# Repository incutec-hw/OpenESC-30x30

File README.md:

# OpenESC-30x30

Open-source 4-in-1 BLDC ESC with a 30.5 × 30.5 mm mounting pattern, built around four independent AT32F421 motor controllers running AM32. Six-layer, DShot over the standard 8-pin connector. Designed in KiCad for JLCPCB assembly.

Part of the incutec OpenDrone line (`incutec-hw/OpenESC-30x30`).

> A smaller **[OpenESC_20X20](https://github.com/incutec-hw/OpenESC_20X20)** (20×20 mm) shares this design and mirrors this repo. The two differ only in board/mounting size and a few power-stage parts.

## Architecture

Four fully independent ESC channels share a common power input and telemetry connector. Each channel has its own MCU and gate driver; the high-current stage is six MOSFETs per channel (three half-bridges). This is the distributed-MCU AM32 4-in-1 topology rather than a single-MCU design. Values below are extracted from the KiCad design files (`hardware/4in1.kicad_sch`, `hardware/ESC.kicad_sch`, `hardware/4in1.kicad_pcb`) and the production BOM (`hardware/production/Rev1-30x30_bom.csv`).

| Block | Part | LCSC | Per board |
|---|---|---|---|
| Motor MCU | AT32F421G8U7 (QFN-28) | C2765098 | 4 |
| Gate driver | NSG2065Q (QFN-24) | C41414478 | 4 |
| Power MOSFETs | SP40N01GHNK PDFN-8L (5×6) | C22385416 | 24 (6 per channel) |

## Specifications

| Parameter | Value |
|---|---|
| Channels | 4 independent BLDC channels |
| MCU | AT32F421G8U7 (ARM Cortex-M4, QFN-28), one per channel |
| Gate driver | NSG2065Q (QFN-24, FD6288Q-compatible), one per channel |
| Power MOSFETs | SP40N01GHNK, N-channel, PDFN-8L (5×6), 24 total (XRS280N03C selected as drop-in next-gen — not yet swapped) |
| Current sense | Board-level high-side: INA186A3IDCKR (100 V/V, SC-70-6) across 2× 0.2 mΩ 2512 shunts in parallel (0.1 mΩ) in the +BATT feed → 10 mV/A → ~330 A full-scale at 3.3 V ADC |
| Input | +BATT direct from connector/pads, 3S–6S |
| Input protection | 3× SMBJ24A TVS (24 V standoff) |
| Buck regulator | LMR54406DBVR (SOT-23-6) + FTC160808S4R7MBCA 4.7 µH inductor → +10 V gate-drive rail (FB 115k/10k, Vref 0.8 V → 10.0 V) |
| LDO | TLV76733DRVR (WSON-6) → +3V3 (MCUs, sensing), from +10 V |
| Signal protocol | DShot (4 independent signal lines, one per channel) |
| Firmware | AM32 (per-channel AT32F421 target, flashed individually) |
| PCB | 6-layer, 1.69 mm |
| Mounting pattern | 30.5 × 30.5 mm, 4× Ø4.0 mm holes (M3) |

Current/voltage ratings are not printed on the design files. The input clamp is set by the SMBJ24A TVS (24 V standoff → 3S–6S); the MOSFET (SP40N01GHNK) and current-sense full-scale (~330 A) set the practical envelope. Characterize before quoting a hard rating.

## Connector

8-pin JST **SM08B-SRSS-TB** (J1). Pin-to-net mapping extracted from the schematic (net labels at the connector pins):

| Pin | Net | Function |
|---|---|---|
| 1 | +BATT | Battery positive |
| 2 | GND | Ground |
| 3 | /CURR | Current-sense telemetry (INA186 output) |
| 4 | *(unconnected)* | No dedicated telemetry pin — telemetry handled by extended DShot |
| 5 | /M1 | DShot signal, channel 1 |
| 6 | /M2 | DShot signal, channel 2 |
| 7 | /M3 | DShot signal, channel 3 |
| 8 | /M4 | DShot signal, channel 4 |

Connector ground returns on the shield/mounting pads P1/P2 (both GND). The same eight signals are also broken out as direct solder pads (U3). Pin 4 — the dedicated telemetry pin on the Betaflight 8-pin standard — is intentionally unconnected: ESC→FC telemetry is carried over the motor signal lines via the bidirectional **extended DShot** protocol.

## Variants and revisions

| File | Description |
|---|---|
| `hardware/4in1.kicad_pro` / `.kicad_pcb` / `.kicad_sch` | Main design (30×30). |
| `hardware/4in1-panel.kicad_pro` / `.kicad_pcb` | Panelized version for production fabrication. |

This repo is the 30×30 member of the OpenESC family; the 20×20 sibling lives in [`OpenESC_20X20`](https://github.com/incutec-hw/OpenESC_20X20). Production exports in `hardware/production/` are versioned `V0.1`–`V0.4` and `Rev1`. `Rev1-30x30` is the 30×30-only fabrication set; `Rev1-30x3020x20` is a combined shared-fab set produced alongside the mini.

## Firmware

[AM32](https://github.com/AlkaMotors/AM32-MultiRotor-ESC-firmware) — incutec's default ESC firmware. Boards ship with the AM32 bootloader pre-loaded; firmware is flashed and configured in-browser at [am32.ca](https://am32.ca). Each channel's AT32F421G8U7 is an independent AM32 target. The AT32F421 + NSG2065Q per-channel topology and the DShot signal nets are the standard AM32 4-in-1 hardware target. Works with Betaflight and other DShot-capable flight controllers.

## Repository structure

```
README.md  LICENSE  CLAUDE.md            Repo root: docs + license + agent instructions
images/                                  Board render images
licensing/                               Hardware license, third-party notices, trademark policy
hardware/                                KiCad 9 project (everything to build/fab the board)
├── 4in1.kicad_sch                       Top schematic (power, current sense, connector)
├── ESC.kicad_sch                        Single ESC channel sheet (instantiated 4×)
├── 4in1.kicad_pcb                       Main board layout (6-layer)
├── 4in1.kicad_pro                       Main project
├── 4in1-panel.kicad_pcb / .kicad_pro    Panelized layout/project for production
├── components.kicad_sym                 Project-local symbol library
├── 4in1ESC-30x30.pretty/                Project-local footprints
├── 4in1ESC-30x30.3dshapes/             3D models (STEP)
├── fp-lib-table / sym-lib-table         Project-local library tables (${KIPRJMOD})
├── 4in1.step / 4in1.glb                 Exported board 3D models
├── production/                          JLCPCB fabrication exports (gerbers, BOM, CPL) per revision
├── fabrication-toolkit-options.json     KiCad Fabrication Toolkit settings
├── cost-analysis.md                     JLCPCB 500-unit cost breakdown (predates latest BOM)
└── database/                            Component analysis notes
```

## License

Hardware: [CERN-OHL-S-2.0](https://ohwr.org/cern_ohl_s_v2.txt). See [LICENSE](LICENSE), [licensing/THIRD_PARTY.md](licensing/THIRD_PARTY.md), and [licensing/TRADEMARKS.md](licensing/TRADEMARKS.md). Some bundled 3D model assets carry their own upstream notices (CC-BY-SA-4.0 / GPL).

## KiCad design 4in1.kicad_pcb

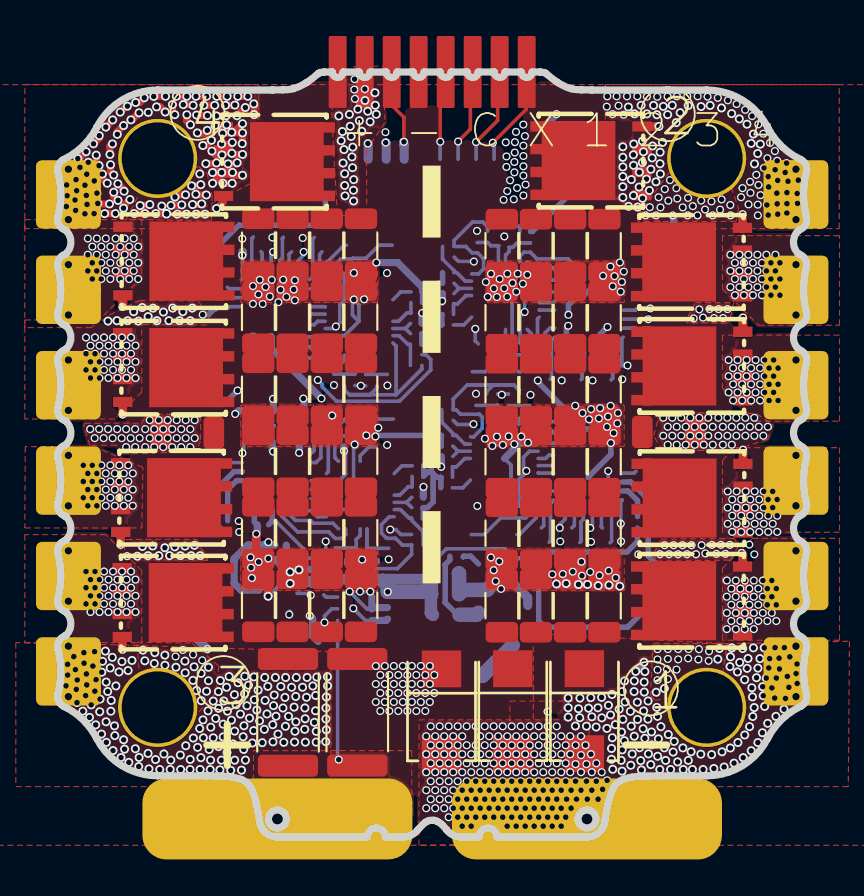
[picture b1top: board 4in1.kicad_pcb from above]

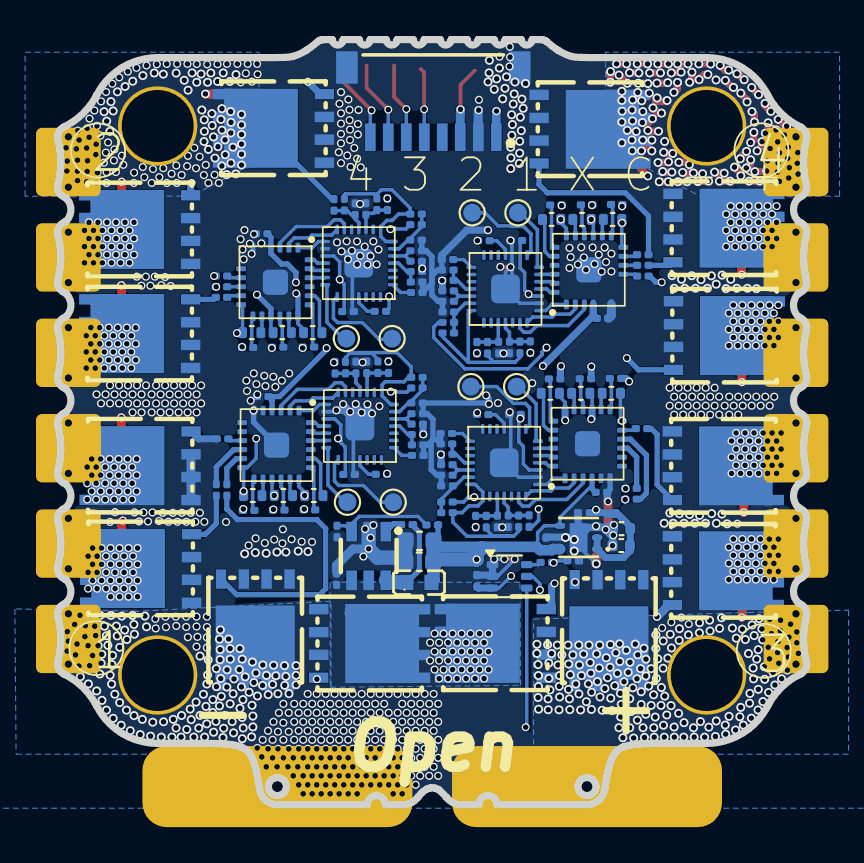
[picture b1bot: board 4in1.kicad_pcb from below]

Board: 6 copper layers, 41.6 x 42.5 mm, 218 parts (152 on the bottom side), 150 nets.

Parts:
C2, C3, C6, C6#2, C6#3, C7, C8, C9, C13, C14, C15, C16, C17, C18, C19, C20, C24, C25, C26, C27, C28, C29, C30, C31, C43, C44, C45, C69, C70, C71, C72, C79, C80, C82, C83, C84, C85, C87, C88, C95, C96, C97, C98, C99, C100, C101, C105, C106, C107, C108: 10uF; C_1206_3216Metric
C4, C51: 22uF; C_0402_1005Metric
C32, C33, C34, C35, C36, C37, C38, C39, C53, C56, C62, C67: 100nF; C_0402_WIDE
C47, C86: 22uF; C_0603_1608Metric
C48, C49, C50, C52, C54, C55, C57, C58, C59, C60, C61, C63, C64, C65, C66, C68, C74, C75, C76, C81, C93, C94: 100nF; C_0201_0603Metric
D1, D2, D3: SMBJ24A; SMB_L4.5-W3.7-LS5.4-RD
J1: SM08B-SRSS-TB; JST_SM08B-SRSS-TB
Q1, Q2, Q3, Q4, Q5, Q6, Q7, Q8, Q9, Q10, Q11, Q12, Q13, Q14, Q15, Q16, Q17, Q18, Q19, Q20, Q21, Q22, Q23, Q24: C22385416; PDFN-8L_L6.0-W5.0-P1.27
R10, R12, R13, R15, R25, R27, R28, R30, R31, R33, R34, R36, R46, R48, R49, R51, R52, R54, R64, R66, R67, R69, R70, R72: 10k; C_0201_0603Metric
R11, R14, R26, R29, R32, R35, R47, R50, R53, R65, R68, R71, R73: 1k; C_0201_0603Metric
R18, R19, R21, R22, R40, R41, R58, R59, R121: 10k; R_0201_0603Metric
R20, R39, R57, R87: 220R; R_0201_0603Metric
R23, R24, R37, R38, R42, R43, R44, R45, R55, R56, R60, R61, R62, R63, R74, R75, R76, R77, R78, R79, R80, R81, R82, R83: 15R; R_0201_0603Metric
R84, R85, R86, R88: 10R; R_0201_0603Metric
R120: 115k; R_0201_0603Metric
Rsense1, Rsense2: 0.2mR; R_2512_6332Metric
TP1, TP2, TP3, TP4, TP5, TP6, TP7, TP8: TestPoint; TestPoint_Pad_D1.0mm
U2, U5, U7, U9: AT32F421G8U7; QFN-28_L4.0-W4.0-P0.40-TL-EP2.4
U3: 4in1ESC30x30
U4, U6, U8, U10: NSG2065Q; QFN-24_L4.0-W4.0-P0.50-TL-EP2.8
U12: INA186A3IDCKR; SOT-363_SC-70-6
U13: LMR54406DBVR; SOT-23-6_L2.9-W1.6-P0.95-LS2.8-BR
U14: FTC160808S4R7MBCA; IND-SMD_L1.6-W0.8_FTC160865SR47MBCA
U15: TLV76733DRVR; WSON-6_L2.0-W2.0-P0.65-TL-EP

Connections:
+3V3: C4.2, C49.1, C51.2, C55.1, C61.1, C66.1, C81.1, C93.1, R18.2, R21.2, R40.2, R58.2, R84.2, R85.2, R86.2, R88.2, U2.17 (VDD), U5.17 (VDD), U7.17 (VDD), U9.17 (VDD), U12.3 (VS), U15.1 (OUT), U15.2 (FB/SNS)
+10V: C47.1, C57.1, C58.1, C63.1, C68.1, C76.1, C86.1, R120.1, U4.4 (VCC), U6.4 (VCC), U8.4 (VCC), U10.4 (VCC), U14.2, U15.4 (EN), U15.6 (IN)
+BATT: C2.1, C3.1, C6.1, C6#2.1, C6#3.1, C7.1, C8.1, C9.1, C13.1, C14.1, C15.1, C16.1, C17.1, C18.1, C19.1, C20.1, C24.1, C25.1, C26.1, C27.1, C28.1, C29.1, C30.1, C31.1, C43.1, C44.1, C45.1, C69.1, C70.1, C71.1, C72.1, C74.1, C79.1, C80.1, C82.1, C83.1, C84.1, C85.1, C87.1, C88.1, C95.1, C96.1, C97.1, C98.1, C99.1, C100.1, C101.1, C105.1, C106.1, C107.1, C108.1, D1.1, D2.1, D3.1, J1.1, Q1.3 (D), Q6.3 (D), Q7.3 (D), Q8.3 (D), Q9.3 (D), Q10.3 (D), Q13.3 (D), Q16.3 (D), Q17.3 (D), Q18.3 (D), Q19.3 (D), Q20.3 (D), Rsense1.2, Rsense2.2, U3.3 (VBAT+), U12.5 (-IN), U13.4 (EN), U13.5 (VIN)
/CSA+: Rsense1.1, Rsense2.1, U3.1 (VBAT), U12.4 (+IN)
/CURR: C94.1, J1.3, R73.1, U3.5 (CUR)
/ESC1/AH: U2.20 (PA10), U4.22 (HIN1)
/ESC1/AL: U2.15 (PB1), U4.1 (LIN1)
/ESC1/BH: U2.19 (PA9), U4.23 (HIN2)
/ESC1/BL: U2.14 (PB0), U4.2 (LIN2)
/ESC1/CH: U2.18 (PA8), U4.24 (HIN3)
/ESC1/CL: U2.13 (PA7), U4.3 (LIN3)
/ESC1/FBA: R25.1, R26.2, R27.2, U2.6 (PA0)
/ESC1/FBB: R28.2, R29.2, R30.2, U2.10 (PA4)
/ESC1/FBC: R31.2, R32.2, R33.2, U2.11 (PA5)
/ESC1/FBCOMMON: R25.2, R28.1, R31.1, U2.7 (PA1)
/ESC1/GHA: R76.1, U4.19 (HO1)
/ESC1/GHB: R55.1, U4.16 (HO2)
/ESC1/GHC: R23.1, U4.13 (HO3)
/ESC1/GLA: R80.1, U4.11 (LO1)
/ESC1/GLB: R62.1, U4.10 (LO2)
/ESC1/GLC: R42.1, U4.9 (LO3)
/ESC1/MotorA: C53.1, Q1.1 (S), Q2.3 (D), R27.1, U3.23 (1A), U4.18 (VS1)
/ESC1/MotorB: C32.1, Q6.1 (S), Q11.3 (D), R30.1, U3.22 (1B), U4.15 (VS2)
/ESC1/MotorC: C36.1, Q16.1 (S), Q21.3 (D), R33.1, U3.21 (1C), U4.12 (VS3)
/ESC1/vdda: C48.1, R84.1, U2.5 (VDDA)
/ESC2/AH: U5.20 (PA10), U6.22 (HIN1)
/ESC2/AL: U5.15 (PB1), U6.1 (LIN1)
/ESC2/BH: U5.19 (PA9), U6.23 (HIN2)
/ESC2/BL: U5.14 (PB0), U6.2 (LIN2)
/ESC2/CH: U5.18 (PA8), U6.24 (HIN3)
/ESC2/CL: U5.13 (PA7), U6.3 (LIN3)
/ESC2/FBA: R10.1, R11.2, R12.2, U5.6 (PA0)
/ESC2/FBB: R13.2, R14.2, R15.2, U5.10 (PA4)
/ESC2/FBC: R34.2, R35.2, R36.2, U5.11 (PA5)
/ESC2/FBCOMMON: R10.2, R13.1, R34.1, U5.7 (PA1)
/ESC2/GHA: R77.1, U6.19 (HO1)
/ESC2/GHB: R56.1, U6.16 (HO2)
/ESC2/GHC: R24.1, U6.13 (HO3)
/ESC2/GLA: R81.1, U6.11 (LO1)
/ESC2/GLB: R63.1, U6.10 (LO2)
/ESC2/GLC: R43.1, U6.9 (LO3)
/ESC2/MotorA: C56.1, Q3.3 (D), Q7.1 (S), R12.1, U3.20 (2B), U6.18 (VS1)
/ESC2/MotorB: C33.1, Q8.1 (S), Q12.3 (D), R15.1, U3.19 (2C), U6.15 (VS2)
/ESC2/MotorC: C37.1, Q17.1 (S), Q22.3 (D), R36.1, U3.18 (2A), U6.12 (VS3)
/ESC2/vdda: C54.1, R85.1, U5.5 (VDDA)
/ESC3/AH: U7.20 (PA10), U8.22 (HIN1)
/ESC3/AL: U7.15 (PB1), U8.1 (LIN1)
/ESC3/BH: U7.19 (PA9), U8.23 (HIN2)
/ESC3/BL: U7.14 (PB0), U8.2 (LIN2)
/ESC3/CH: U7.18 (PA8), U8.24 (HIN3)
/ESC3/CL: U7.13 (PA7), U8.3 (LIN3)
/ESC3/FBA: R46.1, R47.2, R48.2, U7.6 (PA0)
/ESC3/FBB: R49.2, R50.2, R51.2, U7.10 (PA4)
/ESC3/FBC: R52.2, R53.2, R54.2, U7.11 (PA5)
/ESC3/FBCOMMON: R46.2, R49.1, R52.1, U7.7 (PA1)
/ESC3/GHA: R78.1, U8.19 (HO1)
/ESC3/GHB: R60.1, U8.16 (HO2)
/ESC3/GHC: R37.1, U8.13 (HO3)
/ESC3/GLA: R82.1, U8.11 (LO1)
/ESC3/GLB: R74.1, U8.10 (LO2)
/ESC3/GLC: R44.1, U8.9 (LO3)
/ESC3/MotorA: C62.1, Q4.3 (D), Q13.1 (S), R48.1, U3.15 (3B), U8.18 (VS1)
/ESC3/MotorB: C34.1, Q9.1 (S), Q14.3 (D), R51.1, U3.16 (3C), U8.15 (VS2)
/ESC3/MotorC: C38.1, Q18.1 (S), Q23.3 (D), R54.1, U3.17 (3A), U8.12 (VS3)
/ESC3/vdda: C60.1, R86.1, U7.5 (VDDA)
/ESC4/AH: U9.20 (PA10), U10.22 (HIN1)
/ESC4/AL: U9.15 (PB1), U10.1 (LIN1)
/ESC4/BH: U9.19 (PA9), U10.23 (HIN2)
/ESC4/BL: U9.14 (PB0), U10.2 (LIN2)
/ESC4/CH: U9.18 (PA8), U10.24 (HIN3)
/ESC4/CL: U9.13 (PA7), U10.3 (LIN3)
/ESC4/FBA: R64.1, R65.2, R66.2, U9.6 (PA0)
/ESC4/FBB: R67.2, R68.2, R69.2, U9.10 (PA4)
/ESC4/FBC: R70.2, R71.2, R72.2, U9.11 (PA5)
/ESC4/FBCOMMON: R64.2, R67.1, R70.1, U9.7 (PA1)
/ESC4/GHA: R79.1, U10.19 (HO1)
/ESC4/GHB: R61.1, U10.16 (HO2)
/ESC4/GHC: R38.1, U10.13 (HO3)
/ESC4/GLA: R83.1, U10.11 (LO1)
/ESC4/GLB: R75.1, U10.10 (LO2)
/ESC4/GLC: R45.1, U10.9 (LO3)
/ESC4/MotorA: C67.1, Q5.3 (D), Q19.1 (S), R66.1, U3.12 (4A), U10.18 (VS1)
/ESC4/MotorB: C35.1, Q10.1 (S), Q15.3 (D), R69.1, U3.13 (4B), U10.15 (VS2)
/ESC4/MotorC: C39.1, Q20.1 (S), Q24.3 (D), R72.1, U3.14 (4C), U10.12 (VS3)
/ESC4/vdda: C65.1, R88.1, U9.5 (VDDA)
/M1: J1.5, R20.1, U3.7 (M1)
/M2: J1.6, R39.1, U3.8 (M2)
/M3: J1.7, R57.1, U3.9 (M3)
/M4: J1.8, R87.1, U3.10 (M4)
GND: C2.2, C3.2, C4.1, C6.2, C6#2.2, C6#3.2, C7.2, C8.2, C9.2, C13.2, C14.2, C15.2, C16.2, C17.2, C18.2, C19.2, C20.2, C24.2, C25.2, C26.2, C27.2, C28.2, C29.2, C30.2, C31.2, C43.2, C44.2, C45.2, C47.2, C48.2, C49.2, C50.2, C51.1, C52.2, C54.2, C55.2, C57.2, C58.2, C59.2, C60.2, C61.2, C63.2, C64.2, C65.2, C66.2, C68.2, C69.2, C70.2, C71.2, C72.2, C74.2, C76.2, C79.2, C80.2, C81.2, C82.2, C83.2, C84.2, C85.2, C86.2, C87.2, C88.2, C93.2, C94.2, C95.2, C96.2, C97.2, C98.2, C99.2, C100.2, C101.2, C105.2, C106.2, C107.2, C108.2, D1.2, D2.2, D3.2, J1.2, J1.P1 (MP1), J1.P2 (MP2), Q2.1 (S), Q3.1 (S), Q4.1 (S), Q5.1 (S), Q11.1 (S), Q12.1 (S), Q14.1 (S), Q15.1 (S), Q21.1 (S), Q22.1 (S), Q23.1 (S), Q24.1 (S), R11.1, R14.1, R19.2, R22.2, R26.1, R29.1, R32.1, R35.1, R41.2, R47.1, R50.1, R53.1, R59.2, R65.1, R68.1, R71.1, R121.2, U2.16 (VSS), U2.29 (VSS), U3.2 (BATGND), U3.4 (GND), U3.11 (Hole), U4.6 (COM), U4.25 (COM), U5.16 (VSS), U5.29 (VSS), U6.6 (COM), U6.25 (COM), U7.16 (VSS), U7.29 (VSS), U8.6 (COM), U8.25 (COM), U9.16 (VSS), U9.29 (VSS), U10.6 (COM), U10.25 (COM), U12.1 (REF), U12.2 (GND), U13.2 (GND), U15.3 (GND), U15.5 (GND), U15.7 (EP)
unnamed: Q1.2 (G), R76.2
unnamed: Q2.2 (G), R80.2
unnamed: Q3.2 (G), R81.2
unnamed: Q4.2 (G), R82.2
unnamed: Q5.2 (G), R83.2
unnamed: Q6.2 (G), R55.2
unnamed: Q7.2 (G), R77.2
unnamed: Q8.2 (G), R56.2
unnamed: Q9.2 (G), R60.2
unnamed: Q10.2 (G), R61.2
unnamed: Q11.2 (G), R62.2
unnamed: Q12.2 (G), R63.2
unnamed: Q13.2 (G), R78.2
unnamed: Q14.2 (G), R74.2
unnamed: Q15.2 (G), R75.2
unnamed: Q16.2 (G), R23.2
unnamed: Q17.2 (G), R24.2
unnamed: Q18.2 (G), R37.2
unnamed: Q19.2 (G), R79.2
unnamed: Q20.2 (G), R38.2
unnamed: Q21.2 (G), R42.2
unnamed: Q22.2 (G), R43.2
unnamed: Q23.2 (G), R44.2
unnamed: Q24.2 (G), R45.2
unnamed: R19.1, U2.1 (BOOT0)
unnamed: C50.1, R18.1, U2.4 (NRST)
unnamed: TP1.1 (1_1), U2.21 (PA13)
unnamed: TP4.1 (1_1), U2.22 (PA14)
unnamed: R20.2, U2.25 (PB4)
unnamed: C53.2, U4.20 (VB1)
unnamed: C32.2, U4.17 (VB2)
unnamed: C36.2, U4.14 (VB3)
unnamed: R22.1, U5.1 (BOOT0)
unnamed: C52.1, R21.1, U5.4 (NRST)
unnamed: TP2.1 (1_1), U5.21 (PA13)
unnamed: TP5.1 (1_1), U5.22 (PA14)
unnamed: R39.2, U5.25 (PB4)
unnamed: C56.2, U6.20 (VB1)
unnamed: C33.2, U6.17 (VB2)
unnamed: C37.2, U6.14 (VB3)
unnamed: R41.1, U7.1 (BOOT0)
unnamed: C59.1, R40.1, U7.4 (NRST)
unnamed: TP3.1 (1_1), U7.21 (PA13)
unnamed: TP6.1 (1_1), U7.22 (PA14)
unnamed: R57.2, U7.25 (PB4)
unnamed: C62.2, U8.20 (VB1)
unnamed: C34.2, U8.17 (VB2)
unnamed: C38.2, U8.14 (VB3)
unnamed: R59.1, U9.1 (BOOT0)
unnamed: C64.1, R58.1, U9.4 (NRST)
unnamed: TP7.1 (1_1), U9.21 (PA13)
unnamed: TP8.1 (1_1), U9.22 (PA14)
unnamed: R87.2, U9.25 (PB4)
unnamed: C67.2, U10.20 (VB1)
unnamed: C35.2, U10.17 (VB2)
unnamed: C39.2, U10.14 (VB3)
unnamed: R73.2, U12.6 (OUT)
unnamed: C75.2, U13.1 (CB)
unnamed: R120.2, R121.1, U13.3 (FB)
unnamed: C75.1, U13.6 (SW), U14.1

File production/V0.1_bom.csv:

Designator,Footprint,Quantity,Value,LCSC Part #
"C1, C42",0402,2,22uF,C105226
"C2, C3, C6_60, C6_59, C6_58, C6_57, C6_56, C6_55, C6_54, C6_53, C6_52, C6_51, C6_50, C6_49, C6_48, C6_47, C6_46, C6_45, C6_44, C6_43, C6_42, C6_41, C6_40, C6_39, C6_38, C6_37, C6_36, C6_35, C6_34, C6_33, C6_32, C6_31, C6_30, C6_29, C6_28, C6_27, C6_26, C6_25, C6_24, C6_23, C6_22, C6_21, C6_20, C6_19, C6_18, C6_17, C6_16, C6_15, C6_14, C6_13, C6_12, C6_11, C6_10, C6_9, C6_8, C6_7, C6_6, C6_5, C6_4, C6_3, C6_2, C6",1206,62,10uF,C440198
"C32, C33, C34, C35, C36, C37, C38, C39, C53, C59, C73, C83",0402,12,100nF,C307331
C43,0603,1,22uF,C2762594
"C44, C45, C46, C48, C49, C50, C57, C63, C64, C65, C66, C69, C70, C71, C72, C77, C78, C79, C80, C88, C93, C94",0201,22,100nF,C181043
D1,SMB_L4.5-W3.7-LS5.4-RD,1,SMBJ26A_C908802,C908802
"FB1, FB2, FB3, FB4",0201,4,BLM03PX121SN1D,C525479
J1,JST_SM08B-SRSS-TB,1,SM08B-SRSS-TB,C160407
"Q1, Q10, Q11, Q12, Q13, Q14, Q15, Q16, Q17, Q18, Q19, Q2, Q20, Q21, Q22, Q23, Q24, Q3, Q4, Q5, Q6, Q7, Q8, Q9",PDFN-8L_L6.0-W5.0-P1.27,24,C22385416,SP40N01GHNK
"R1, R16, R17, R2, R21, R22, R23, R24, R37, R38, R42, R43, R44, R45, R55, R56, R6, R60, R61, R62, R63, R7, R8, R9",0201,24,8R,C473542
"R10, R118, R12, R13, R15, R18, R19, R25, R27, R28, R3, R30, R31, R33, R34, R36, R39, R4, R40, R46, R48, R49, R51, R52, R54, R57, R58, R64, R66, R67, R69, R70, R72",0201,33,10k,C473048
"R11, R14, R26, R29, R32, R35, R47, R50, R53, R65, R68, R71, R73",0201,13,1k,C270365
R119,0201,1,124k,C423759
"R20, R41, R5, R59",0201,4,220R,C473535
RSENSE1,2512,1,0.2mR,C695806
"TP1, TP2, TP3, TP4, TP5, TP6, TP7, TP8",TestPoint_Pad_D1.0mm,8,TestPoint,
U1,WSON-6_L2.0-W2.0-P0.65-TL-EP,1,TLV76733DRVR,C2848334
"U10, U2, U6, U8",QFN-28_L4.0-W4.0-P0.40-TL-EP2.4,4,AT32F421G8U7,C2765098
"U11, U4, U7, U9",QFN-24_L4.0-W4.0-P0.50-TL-EP2.8,4,NSG2065Q,C41414478
U12,SOT-363_SC-70-6,1,INA186A3IDCKR,C2058245
U18,SOT-23-6_L2.9-W1.6-P0.95-LS2.9-BL,1,LMR51420YDDCR,C7296200
U3,4in1ESC30x30,1,~,
U5,IND-SMD_L1.6-W0.8_FTC160865SR47MBCA,1,XRIM160808SR47MBCD,C48391583

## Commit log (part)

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2026-03-14 Revise status section in README.md
    Updated project status and removed completed tasks.
2026-03-14 add images
2026-03-14 better pics
2026-03-16 Final parts changes and production files for V0.1
2026-05-07 alpha routing
2026-06-06 New routing
2026-06-06 pcb: routing snapshot (WIP) before hardware/ restructure
    Snapshot of in-progress PCB routing so the upcoming directory
    restructure can move the file as a clean rename. Routing is still
    in progress.
